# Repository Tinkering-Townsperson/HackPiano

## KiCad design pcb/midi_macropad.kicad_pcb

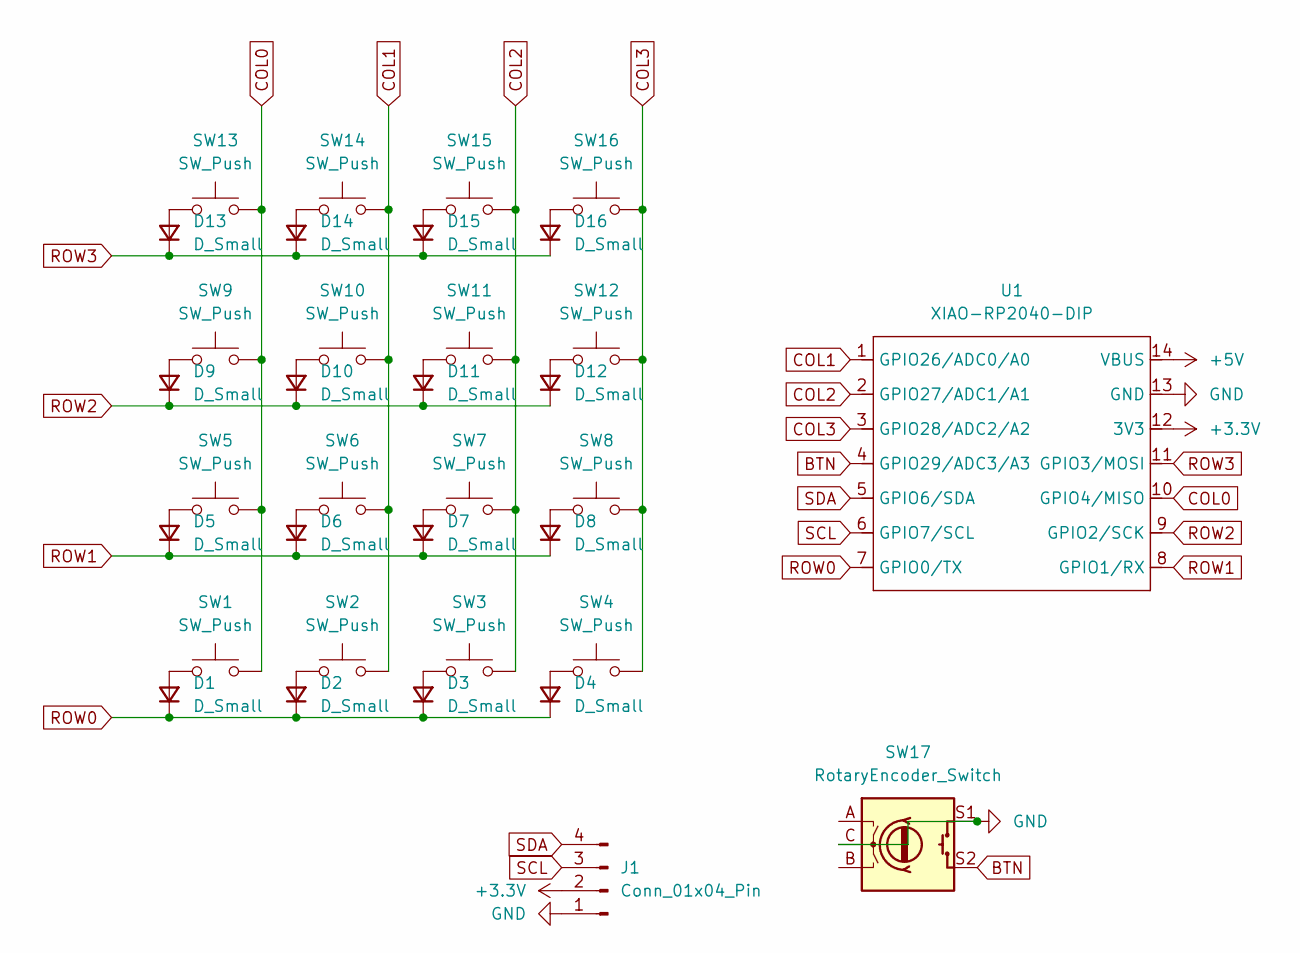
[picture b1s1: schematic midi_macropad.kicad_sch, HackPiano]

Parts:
D1, D2, D3, D4, D5, D6, D7, D8, D9, D10, D11, D12, D13, D14, D15, D16: D_Small; D_DO-35_SOD27_P7.62mm_Horizontal
J1: Conn_01x04_Pin; SSD1306-0.91-OLED-4pin-128x32
SW1, SW2, SW3, SW4, SW5, SW6, SW7, SW8, SW9, SW10, SW11, SW12, SW13, SW14, SW15, SW16: SW_Push; SW_Cherry_MX_1.00u_PCB
SW17: RotaryEncoder_Switch; RotaryEncoder_Alps_EC11E-Switch_Vertical_H20mm
U1: XIAO-RP2040-DIP

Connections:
+3.3V: J1.2, U1.12 (3V3)
+5V: U1.14 (VBUS)
BTN: SW17.S2, U1.4 (GPIO29/ADC3/A3)
COL0: SW1.2, SW5.2, SW9.2, SW13.2, U1.10 (GPIO4/MISO)
COL1: SW2.2, SW6.2, SW10.2, SW14.2, U1.1 (GPIO26/ADC0/A0)
COL2: SW3.2, SW7.2, SW11.2, SW15.2, U1.2 (GPIO27/ADC1/A1)
COL3: SW4.2, SW8.2, SW12.2, SW16.2, U1.3 (GPIO28/ADC2/A2)
GND: J1.1, SW17.C, SW17.S1, U1.13 (GND)
unnamed: D1.2 (A), SW1.1
unnamed: D2.2 (A), SW2.1
unnamed: D3.2 (A), SW3.1
unnamed: D4.2 (A), SW4.1
unnamed: D5.2 (A), SW5.1
unnamed: D6.2 (A), SW6.1
unnamed: D7.2 (A), SW7.1
unnamed: D8.2 (A), SW8.1
unnamed: D9.2 (A), SW9.1
unnamed: D10.2 (A), SW10.1
unnamed: D11.2 (A), SW11.1
unnamed: D12.2 (A), SW12.1
unnamed: D13.2 (A), SW13.1
unnamed: D14.2 (A), SW14.1
unnamed: D15.2 (A), SW15.1
unnamed: D16.2 (A), SW16.1
ROW0: D1.1 (K), D2.1 (K), D3.1 (K), D4.1 (K), U1.7 (GPIO0/TX)
ROW1: D5.1 (K), D6.1 (K), D7.1 (K), D8.1 (K), U1.8 (GPIO1/RX)
ROW2: D9.1 (K), D10.1 (K), D11.1 (K), D12.1 (K), U1.9 (GPIO2/SCK)
ROW3: D13.1 (K), D14.1 (K), D15.1 (K), D16.1 (K), U1.11 (GPIO3/MOSI)
SCL: J1.3, U1.6 (GPIO7/SCL)
SDA: J1.4, U1.5 (GPIO6/SDA)

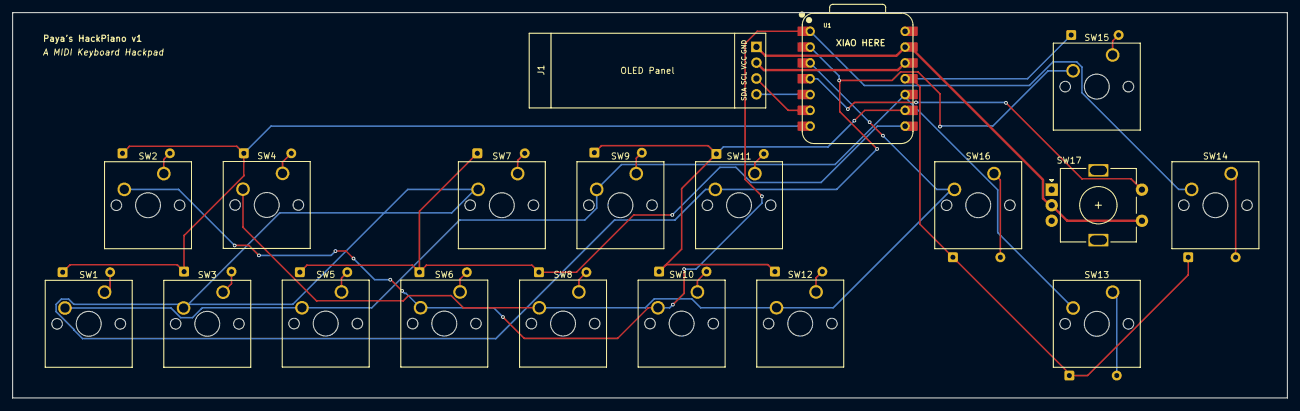
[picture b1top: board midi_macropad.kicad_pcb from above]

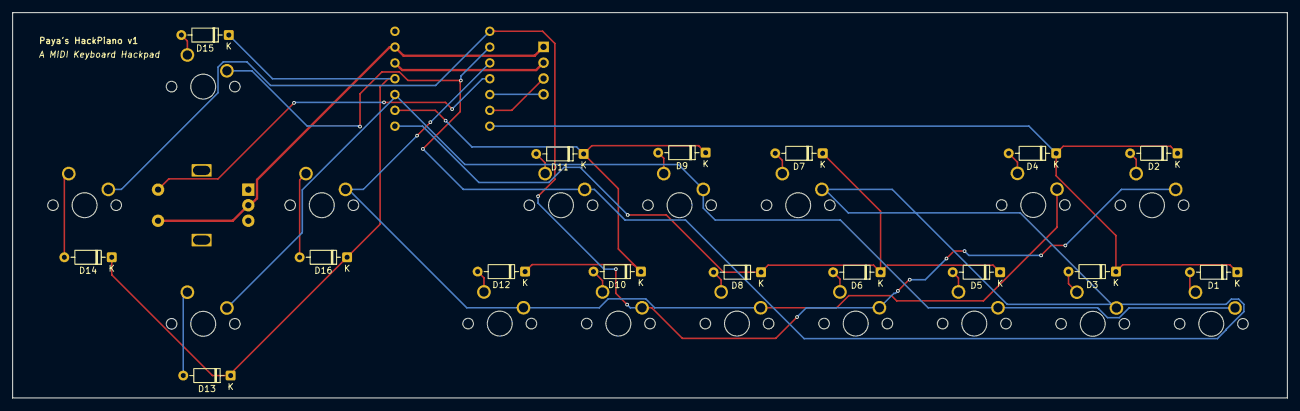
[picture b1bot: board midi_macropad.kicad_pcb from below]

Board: 2 copper layers, 204.8 x 61.9 mm, 35 parts (16 on the bottom side), 29 nets.

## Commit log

2025-07-02 fix: Change `edge.cuts` to a rectangle for easier measurement
2025-07-02 feat: Create keyboard layout
2025-07-02 feat: Design and export HackPiano case base
2025-07-02 feat: Design and export HackPiano case top
2025-07-04 feat: Add viewable STL files
2025-07-04 feat: Get started on firmware
    Still todo:
    - OLED display
    - sustain pushbutton
2025-07-06 feat: Add OLED functionality
2025-07-06 refactor: Future-proof variable names
2025-07-06 refactor: Mostly type-checking stuff
2025-07-06 docs: Add docstrings and fix typos
2025-07-06 style: Put control change things together for readability
2025-07-06 fix: Remove references to non-existing `button` module
